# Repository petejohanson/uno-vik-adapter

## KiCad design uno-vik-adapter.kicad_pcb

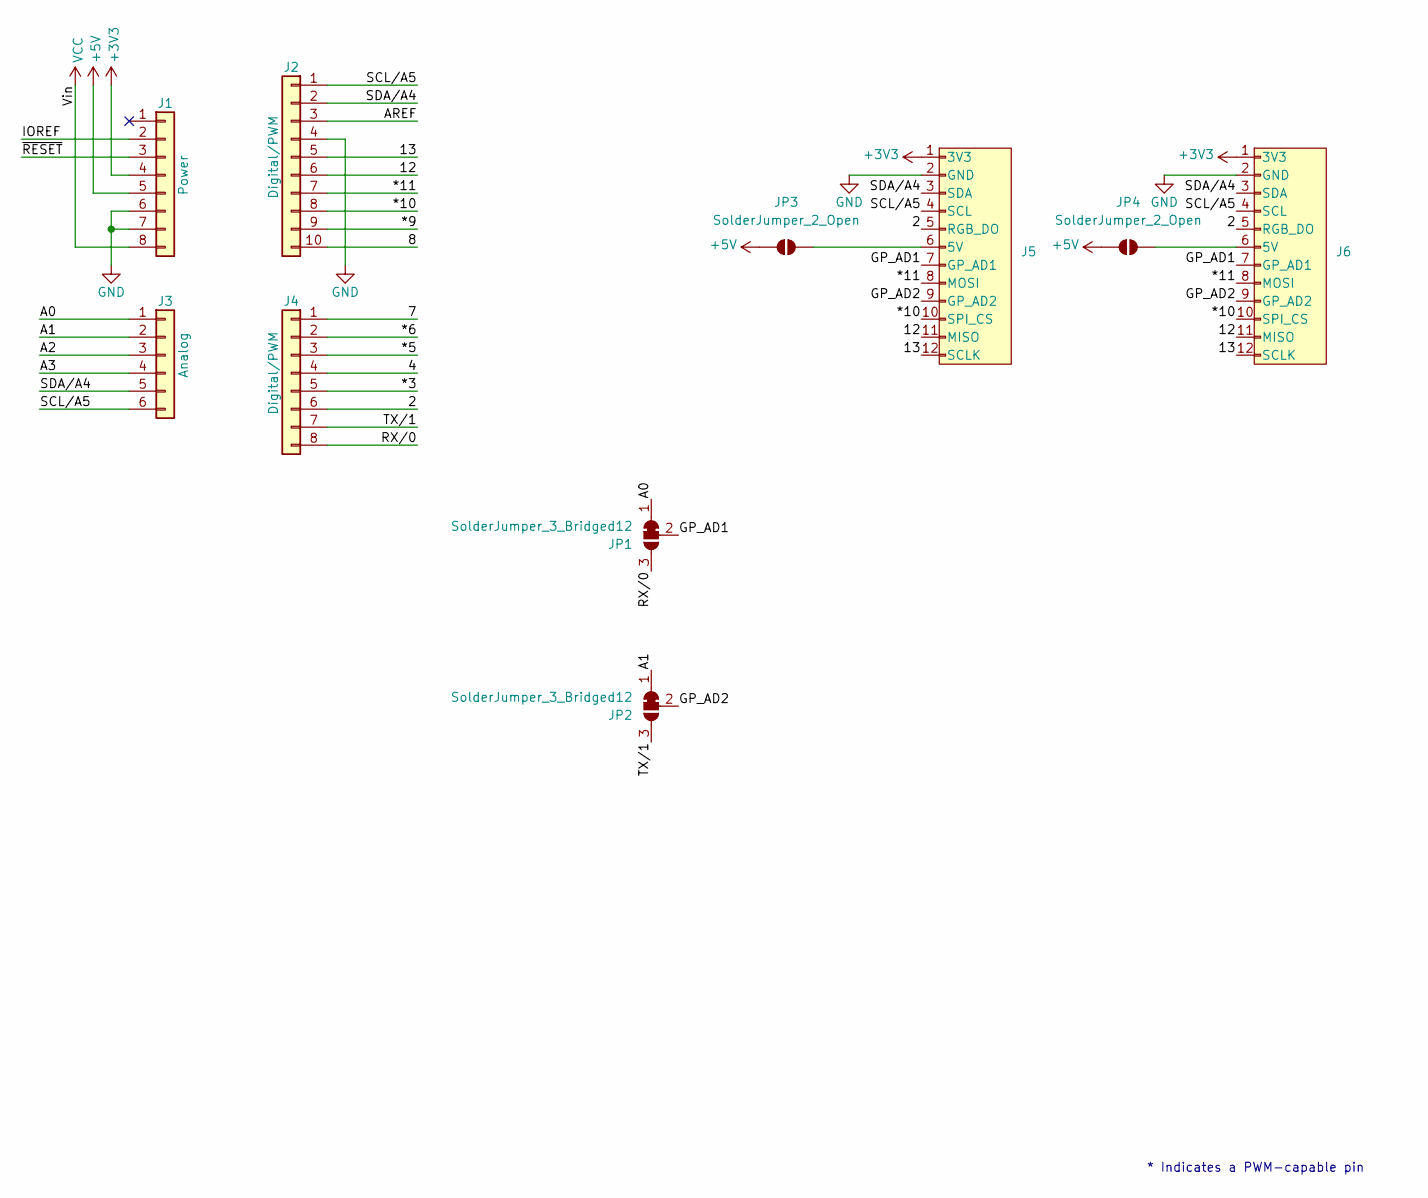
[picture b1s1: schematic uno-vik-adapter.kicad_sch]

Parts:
J1: Power; PinSocket_1x08_P2.54mm_Vertical
J2: Digital/PWM; PinSocket_1x10_P2.54mm_Vertical
J3: Analog; PinSocket_1x06_P2.54mm_Vertical
J4: Digital/PWM; PinSocket_1x08_P2.54mm_Vertical
J5, J6: vik-keyboard-connector-horizontal; LCSC Part Number C479750
JP1, JP2: SolderJumper_3_Bridged12; SolderJumper-3_P1.3mm_Bridged12_RoundedPad1.0x1.5mm
JP3, JP4: SolderJumper_2_Open; SolderJumper-2_P1.3mm_Open_TrianglePad1.0x1.5mm

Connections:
+3V3: J1.4, J5.1 (3V3), J6.1 (3V3)
+5V: J1.5, JP3.1 (A), JP4.1 (A)
/2: J4.6, J5.5 (RGB_DO), J6.5 (RGB_DO)
/4: J4.4
/7: J4.1
/8: J2.10
/12: J2.6, J5.11 (MISO), J6.11 (MISO)
/13: J2.5, J5.12 (SCLK), J6.12 (SCLK)
/*3: J4.5
/*5: J4.3
/*6: J4.2
/*9: J2.9
/*10: J2.8, J5.10 (SPI_CS), J6.10 (SPI_CS)
/*11: J2.7, J5.8 (MOSI), J6.8 (MOSI)
/A0: J3.1, JP1.1 (A)
/A1: J3.2, JP2.1 (A)
/A2: J3.3
/A3: J3.4
/AREF: J2.3
/GP_AD1: J5.7 (GP_AD1), J6.7 (GP_AD1), JP1.2 (C)
/GP_AD2: J5.9 (GP_AD2), J6.9 (GP_AD2), JP2.2 (C)
/IOREF: J1.2
/RX/0: J4.8, JP1.3 (B)
/SCL/A5: J2.1, J3.6, J5.4 (SCL), J6.4 (SCL)
/SDA/A4: J2.2, J3.5, J5.3 (SDA), J6.3 (SDA)
/TX/1: J4.7, JP2.3 (B)
/~RESET: J1.3
GND: J1.6, J1.7, J2.4, J5.2 (GND), J6.2 (GND)
unnamed: J5.6 (5V), JP3.2 (B)
unnamed: J6.6 (5V), JP4.2 (B)
VCC: J1.8

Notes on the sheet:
* Indicates a PWM-capable pin

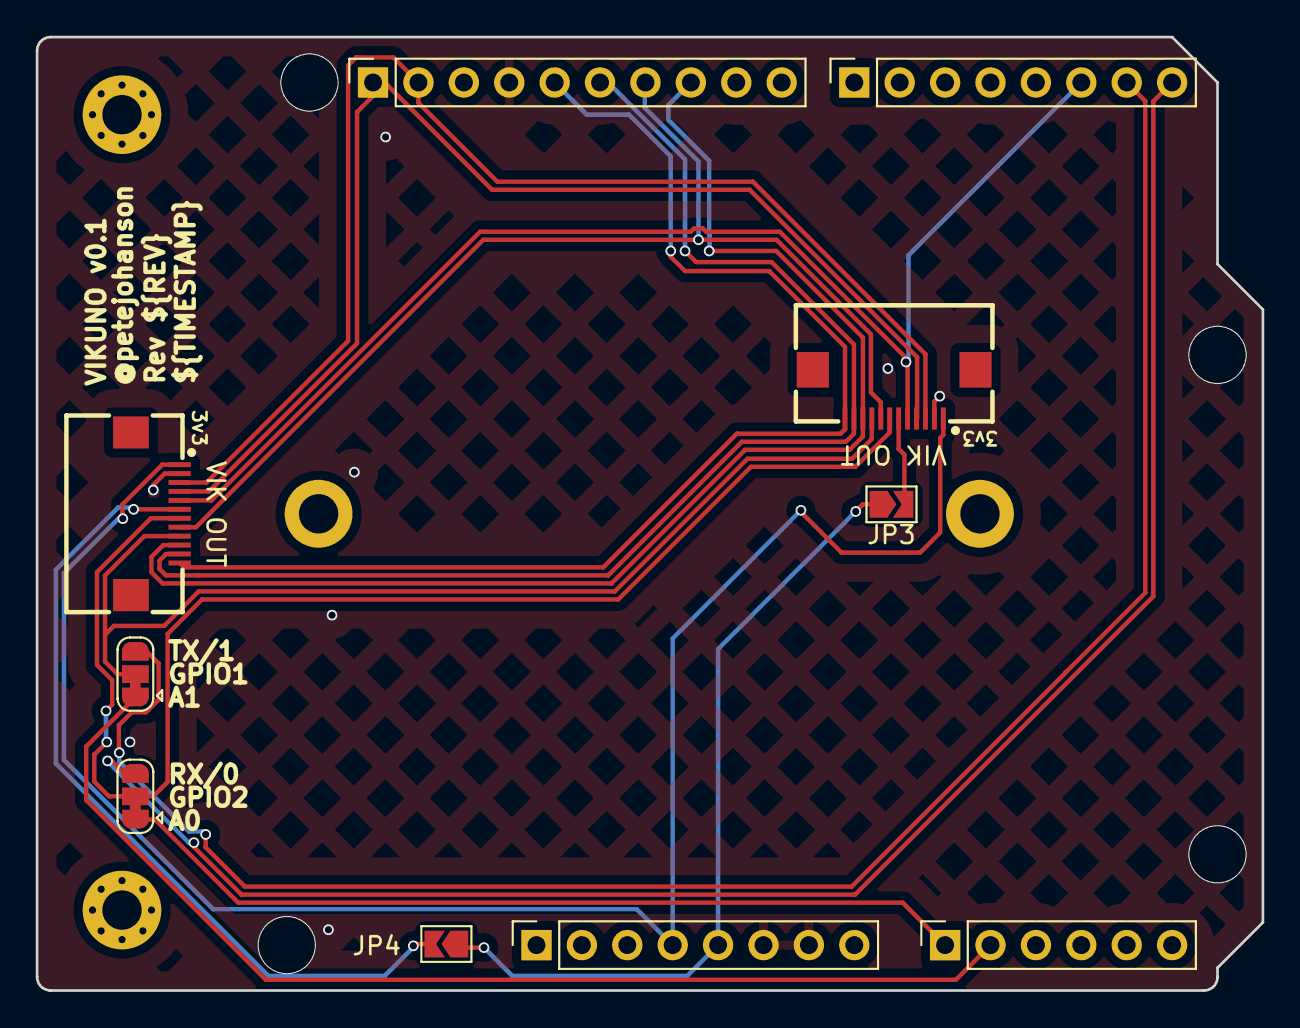
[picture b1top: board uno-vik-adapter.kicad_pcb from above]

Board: 2 copper layers, 68.6 x 53.3 mm, 17 parts (0 on the bottom side), 18 nets.

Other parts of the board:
MH1, MH2, MH3, MH4: MountingHole_3.2mm
VMH1: vik-module-mounting-small
VMH2, VMH3: MountingHole_2.2mm_M2_Pad_Via

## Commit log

2024-03-25 Initial import.
2024-03-25 Docker image bump.
2024-03-25 Tweaks to refs.
2024-03-25 File path fixes.
2024-08-24 Tweaks.
2024-08-28 Add jumpers for 5v pin.
2024-08-28 Move away from deprecated actions.
2024-08-28 fix: Distinct artifact names.
